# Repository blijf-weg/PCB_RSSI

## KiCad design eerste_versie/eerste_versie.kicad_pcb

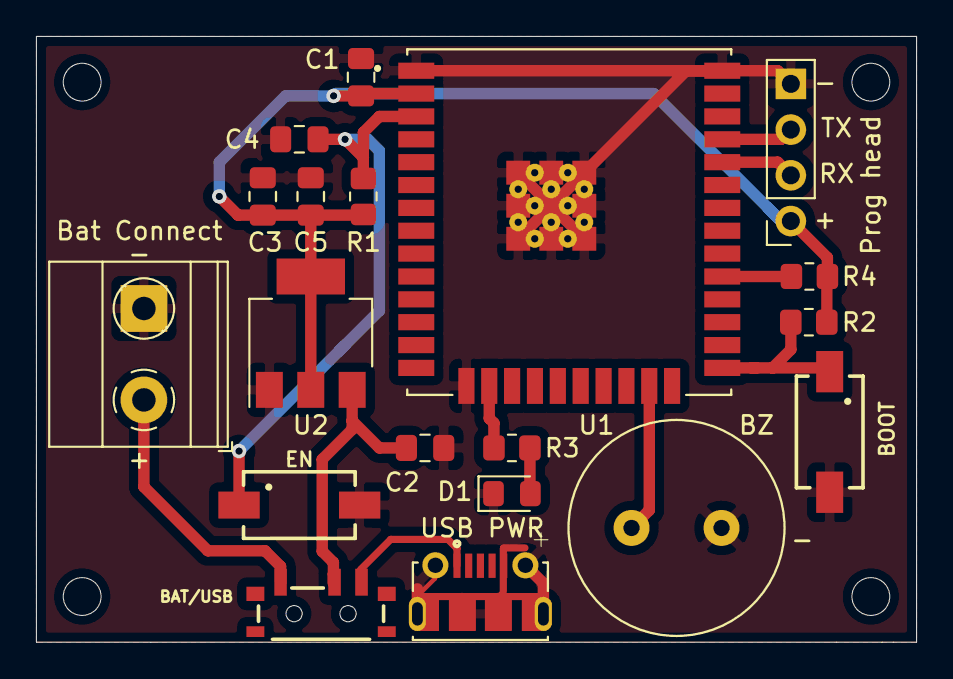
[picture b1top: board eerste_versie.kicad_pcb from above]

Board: 2 copper layers, 48.9 x 33.7 mm, 23 parts (0 on the bottom side), 13 nets.

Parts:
1, 2, 3, 4: MountingHole_2.1mm
BAT/USB: SW_DPDT_x2; SWITCH_SPST_SMD_A
BOOT: SW_DIP_x01; 434111043826
BZ: Buzzer; CUI_CPT-1255C-090
Bat Connect: Conn_01x02; TerminalBlock_Phoenix_MKDS-1,5-2-5.08_1x02_P5.08mm_Horizont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
C1, C5: 100n; C_0805_2012Metric_Pad1.18x1.45mm_HandSolder
C2, C3: 10uF; C_0805_2012Metric_Pad1.18x1.45mm_HandSolder
C4: 1u; C_0805_2012Metric_Pad1.18x1.45mm_HandSolder
D1: LED; LED_0805_2012Metric_Pad1.15x1.40mm_HandSolder
EN: SW_DIP_x01; 434111043826
Prog head: Conn_01x04; PinSocket_1x04_P2.54mm_Vertical
R1, R2, R4: 10k; R_0805_2012Metric_Pad1.20x1.40mm_HandSolder
R3: TBD; R_0805_2012Metric_Pad1.20x1.40mm_HandSolder
U1: ESP32-WROOM-32U; XCVR_ESP32-WROOM-32U
U2: AMS1117-3.3; SOT-223-3_TabPin2
USB PWR: 105017-1001; MOLEX_105017-1001

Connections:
BAT_PWR: BAT/USB.3, Bat Connect.1
GND: BOOT.2, BZ.2, Bat Connect.2, C1.1, C2.2, C3.2, C4.2, C5.1, D1.1, EN.2, Prog head.4, U1.1, U1.15, U1.38, U1.G.1, U1.G.2, U1.G.4, U1.G.5, U1.G.6, U1.G.7, U1.G.8, U1.G.9, U1.G.10, U1.G.11, U1.G.12, U1.G.13, U1.G.14, U1.G.15, U1.G.16, U1.G.17, U1.G.18, U1.G.19, U1.G.20, U1.G.21, U1.G.22, U2.1, USB PWR.5, USB PWR.S1, USB PWR.S2, USB PWR.S3, USB PWR.S4, USB PWR.S5, USB PWR.S6
unnamed: BOOT.1, R2.2, U1.25
unnamed: BZ.1, U1.23
unnamed: BAT/USB.2, C2.1, U2.3
unnamed: C4.1, EN.1, R1.2, U1.3
unnamed: D1.2, R3.1
unnamed: Prog head.2, U1.34
unnamed: Prog head.3, U1.35
unnamed: R3.2, U1.16
unnamed: R4.2, U1.29
USB_PWR: BAT/USB.1, USB PWR.1
VDD33: C1.2, C3.1, C5.2, Prog head.1, R1.1, R2.1, R4.1, U1.2, U2.2

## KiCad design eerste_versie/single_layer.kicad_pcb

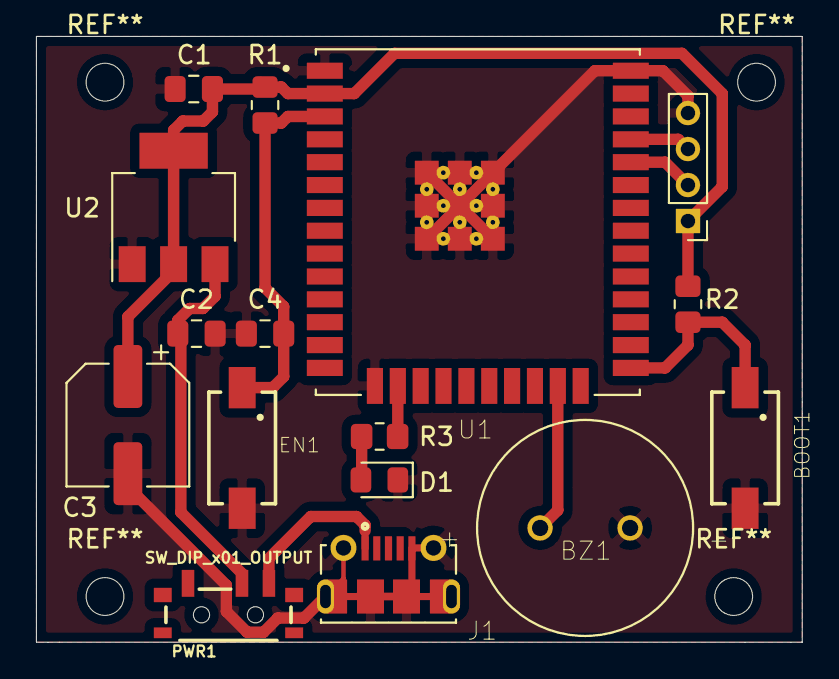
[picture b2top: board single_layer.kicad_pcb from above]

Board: 2 copper layers, 42.5 x 33.7 mm, 16 parts (0 on the bottom side), 11 nets.

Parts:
BOOT1: SW_DIP_x01; 434111043826
BZ1: Buzzer; CUI_CPT-1255C-090
C1, C2: 100n; C_0805_2012Metric_Pad1.18x1.45mm_HandSolder
C3: 47u; CP_Elec_6.3x3
C4: 1u; C_0805_2012Metric_Pad1.18x1.45mm_HandSolder
D1: LED; LED_0805_2012Metric_Pad1.15x1.40mm_HandSolder
EN1: SW_DIP_x01; 434111043826
J1: 105017-1001; MOLEX_105017-1001
PWR1: SW_DIP_x01_OUTPUT; SWITCH_SPST_SMD_A
Programmer_Header1: Conn_01x04; PinHeader_1x04_P2.00mm_Vertical
R1, R2: 10k; R_0805_2012Metric_Pad1.20x1.40mm_HandSolder
R3: TBD; R_0805_2012Metric_Pad1.20x1.40mm_HandSolder
U1: ESP32-WROOM-32U; XCVR_ESP32-WROOM-32U
U2: AMS1117-3.3; SOT-223-3_TabPin2

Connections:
GND: BOOT1.2, BZ1.2, C1.1, C2.2, C3.2, C4.2, D1.1, EN1.2, J1.5, J1.S1, J1.S2, J1.S3, J1.S4, J1.S5, J1.S6, Programmer_Header1.4, U1.1, U1.15, U1.38, U1.G.1, U1.G.2, U1.G.4, U1.G.5, U1.G.6, U1.G.7, U1.G.8, U1.G.9, U1.G.10, U1.G.11, U1.G.12, U1.G.13, U1.G.14, U1.G.15, U1.G.16, U1.G.17, U1.G.18, U1.G.19, U1.G.20, U1.G.21, U1.G.22, U2.1
unnamed: BOOT1.1, R2.2, U1.25
unnamed: BZ1.1, U1.23
unnamed: C2.1, PWR1.2, U2.3
unnamed: C4.1, EN1.1, R1.2, U1.3
unnamed: D1.2, R3.1
unnamed: J1.1, PWR1.1
unnamed: Programmer_Header1.2, U1.34
unnamed: Programmer_Header1.3, U1.35
unnamed: R3.2, U1.16
VDD33: C1.2, C3.1, Programmer_Header1.1, R1.1, R2.1, U1.2, U2.2

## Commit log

2021-03-07 PCB ontwerp voor RSSI afstandsmetignen
2021-03-07 schema opgekuisd
2021-03-09 100n condensatoren van footprint gewijzigd
2021-03-16 tweede versie
2021-03-17 derde_versie
2021-03-23 volledige versie
2021-03-23 nog een kleine aanpassing
2021-03-24 om te printen
2021-03-24 om te printen 2
2021-04-09 batterij toevoeging
    - printkroonsteentje voor aansluiting van batterijkabels toegevoegd
    - pull-up weerstand aan IO5 toegevoegd
    -3D modellen toegevoegd
    - silkscreens in orde gebracht
2021-04-09 snelle aanpassing
    - twee silkscreen namen versleept
2021-04-09 schema opgekuist
2021-04-12 feedback verbeterd
2021-04-12 grondvlak terug toegevoegd
2021-04-12 finaal ontwerp
2021-04-12 doorgestuurde versie
2021-04-24 opgemaakte versie voor github verslag
